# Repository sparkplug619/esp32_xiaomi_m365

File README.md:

attention - last update of this repo - i moved it to gitlab -> https://gitlab.com/esp32m365/esp32_xiaomi_m365_display

# esp32_xiaomi_m365
Sample Project for decoding serial bus data on a Xiaomi M365 Scooter on Espressif ESP32:
- Supports one or two 0.96" 128x64 SSD1306 based OLED screen(s)
- Display connectivity via i2c or spi (spi preffered as it's much faster)
- Firmwareupdates (of the ESP32) can be done over WiFi using ArduinoOTA, Scooterfirmwareupdates are not blocked, can be done the usual way
- Connects to known WiFi Networks or opens it's own SSID in AP Mode
- optional Telnet Servers for debugging
- Config Menu for changing scooter & esp settings
- Supports different Screen Languages, Miles/Kilometers, Wheel Sizes, 10/12s batteries
- Alerts for Low Battery, ESC, BMS Temperature, Cell-Voltage Monitoring,...
- displays speeds above 32.768km/h (set for speeds from 10km/h backwards to 55,44km/h forward, backwardspeed is displayed as a positive number)

# Details
- Telnet on Port 36523 with different Screens
- Telnet on Port 36524 with raw byte dump from M365 Bus ("read only")
- Telnet on Port 36525 with packet decode/dump from M365 Bus ("read only")
- M365 Serial Receiver and Packet decoder into Array per Address
- M365 Data Requestor obey the M365 Bus Timing, does not interfere with Xiaomi's Firmware-Flash process, but can be disabled in the menu (ESP Bus Mode = Passive)
- Data Requestor internally allows subscription to predefined groups of data (e.g. OLED display only needs Cell-Voltage Data when it's displayed) to reduce requested data and therefore get a higher update rate on the interesting data fields.
- Internal Timers/Counters for debugging Receiver/Requestor & Oled-Draw/Transfer Durations - see Telnet/36523 Statistics Screen
- Different Screens for Drive/Stop/Charge/Error/Firmwareupgrade/Locked State/Timeout-Screen
- Alerts: Background Task ("Housekeeper") periodically requests additional data from M365 and validates against tresholds (set in configmenu), shows alert-popup and increases alert-counters
- Popups on screen if alerts occur, alert-counters in data screens when stopped
- Scooter can be locked/unlocked/switched off from config-menu
- Custom Screens for
	- Driving
	- "Stopped" - multiple Data screens when not moving (swipe through them using throttle)
	- "Charging" - in single-screen configuration multiple screens while charging (swipe through them using throttle)
	- Config Menu (push Brake & Throttle at the same time to enter, select items using throttle, change/enter using brake)
 	- "LOCKED" screen mode when scooter has been locked

# Todos
 - add display-sleeptimer - x seconds after last event (gas/brake/throttle/speed/chargerun-plug/telnet/AP-Client Connection & speed = 0)

# Telnet / Debugging Interface
 - Telemetrie Screen shows decoded known values: Batt Voltage, Current, Speed,... 
 - Statistics Screen dumps some internal counters, e.g. Packet Counters, CRC Files, Timing,...
 - ESC/BLE/BMS/"X1" RAW Screens dumps the 512 Byte Array for each device (format "00 00 ...")

 use the letters
  - s,t,e,b,n,x to switch between the screens
  - r to reset statistics & zero m365 data arrays

# Wiring
## Connector in M365 Headunit
M365 has a Serial Data Bus over one Wire (UART in half-duplex mode) between BLE Module and ESC (Motor Controller) and we want to connect the ESP32 to that bus, as well as get Power from the Scooter.
The Connection between BLE-Module and ESC consists of 4 wires, the connection as seen on the BLE Module:
- Ground  (Black, "G")
- One Wire Serial Connection (Yellow, "T", 115200bps, 8n1)
- VBatt (Green, "P", always available)
- 5V (Red, "5", only when scooter is turned on)

## ESP32 Powering
ESP32 needs a Vcc of 3.3V, so you can wire the 5V from M365 to a Vreg for 3.3v which powers the ESP. DO NOT POWER THE ESP32 WITH 5V!

## M365 Serial Data Bus Connection

Other then the VCC which can not be 5V, the ESP32 GPIO Pins can be connected to 5V signals.
So the Serial RX & TX Pins can be directly connected, but to ensure communication on the one-wire uart bus we need 2, to be on the safe side 3 parts:
 - 680R or 1k between RX and M365 Data Bus
 - And a Diode from M365 Data Bus in series with a ~100-200R towards TX Pin of  ESP32
That way Hardware-UART on the ESP32 can be used.

## ESP32 Pin assignment

The ESP32 has a io-switchmatrix, so (nearly) any hardwareunit can be mapped to nearly any pin.
Just be sure to not to use:
 - GPIO_NUM_34 – GPIO_NUM_39 are only GPI - Input, NO OUTPUT, No Pullup or Pulldown!
 - GPIO 6-11 are used by flash - not usable
 - GPIO 0 is for boot/flashing with pullup

# PCB Bugs v180723
 - 1nF or 470pF C from EN towards GND and 12-18k R from EN towards 3.3V are missing (sad copy and paste error)
 - the SOT23 Diode housing might be wrong - depending on your Diode (BAS70xx versions) -> the Diode-Package can be rotated 120° CCW to fix that

# Before Compiling

## Choose your environment  (platformio):
  - PlatformIO supports different (build-)"Environments", you will mostly want to select "m365client" which implements the "client" for a stock m365 scooter and the oled display.
## PATCH your libraries!
  - Plattformio includes my patched Adafuit_SSD1306 library for you, if u are using a different ide, please look in platformio.ini for references to the patches libraries and make sure those are used. In the meanwhile Adafruit updated it's libraries to get rid of the problems, so one day i'll update my code to use the new lib from Adafruit and get rid of the patched libraries.
  - earlier code versions needed some files patched in arduino-esp32 framework in order for correct uart functionality. now i've included the patched UART-Files in this repo, so the patch in arduino-esp32 is not needed anymore (save you time and solves the problem that your other projects would also use that patched framework). But one day when arduino-esp32 framework get's updated this might brake and the files included in this project need to be updated.
  - unfortunately the latest update of platform-io included the arduino-esp32 framework with a broken i2c implementation. This needs to be patched manually, but it fixes a general problem, so this will help your other projects using i2c as well. For patching please see this issue and replace the 4 files as mentioned - otherwise the i2c-display will hang at most restarts: https://github.com/platformio/platform-espressif32/issues/126

## setup individual settings
### ssid's and passwords:
 - please open secrets.h and fill in your own ssid/passwords for client/ap mode and ota updates!
### setup for your hardware
 - copy one of my board*.h files that fits your hardware best, update it for your setup and include this file in definitions.h
 - when updating my code you just need to reapply the include of your boards file in definitions.h

# Support, Questions,...?
 - Telegram Group https://t.me/esp32brain4m365

# Credits & Thanks to
 - Paco Gorina for his research on the protocoll and packet structure (-> http://www.gorina.es/9BMetrics/)
 - CamiAlfa for his research and providing informations about the contents of the packets & arrays (-> https://github.com/CamiAlfa/M365-BLE-PROTOCOL)
 - french translation kindly provided by Technoo' Loggie (Telegram Handle @TechnooLoggie)

# Licensed under Creative Commons V4 - BY NC SA
 - THIS MEANS YOU CAN USE THIS CODE FOR NON COMMERCIAL PURPOSES, HAVE TO RESHARE YOUR MODIFICATIONS AND REFERENCE THIS REPO.

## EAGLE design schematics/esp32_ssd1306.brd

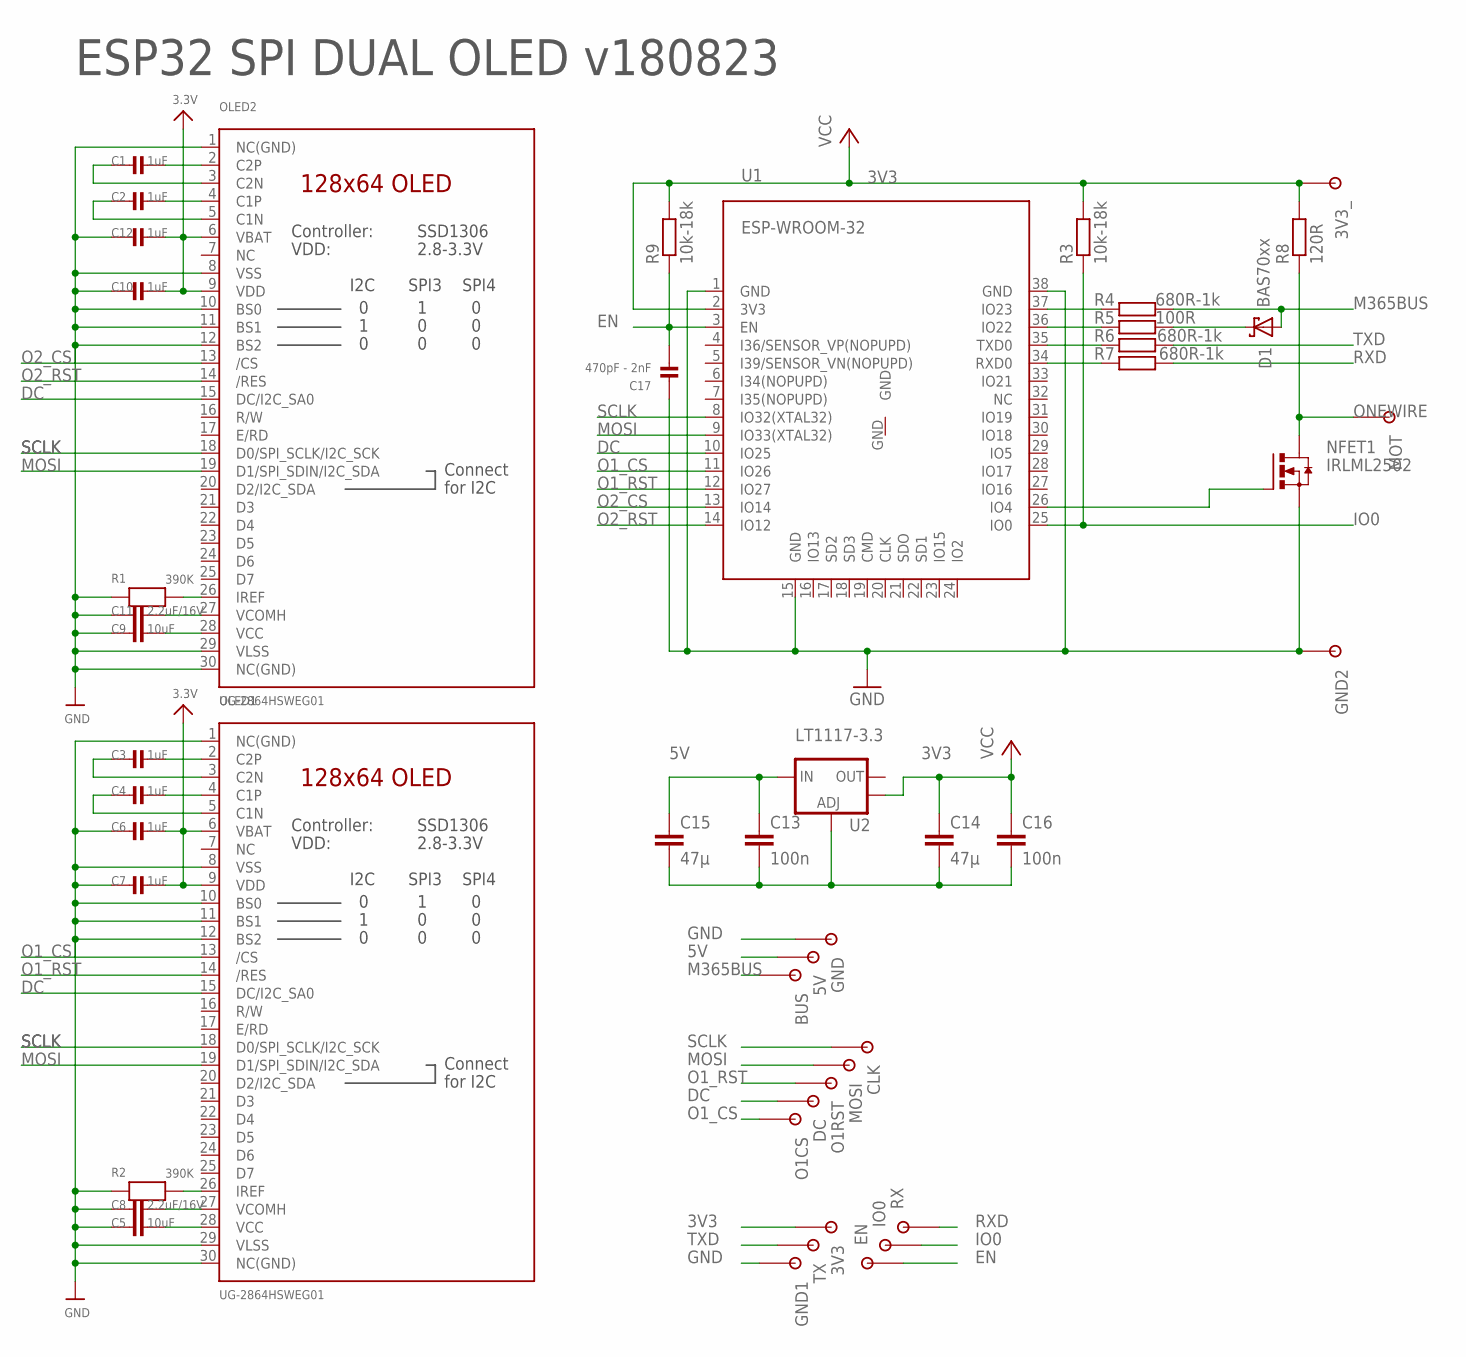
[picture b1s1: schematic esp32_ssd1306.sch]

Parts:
3V3, 3V3_, 5V: PAD1
BUS: PAD1
C1, C2, C3, C4, C6, C7, C10, C12: 1uF; 0805
C5, C9: 10uF; 0805
C8, C11: 2.2uF/16V; 0805
C13, C16: 100n; C0805K
C14, C15: 47µ; C1210K
C17: 470pF - 2nF; 0805
CLK: PAD1
D1: BAS70xx; SOT23
DC: PAD1
EN: PAD1
GND, GND1, GND2: PAD1
IO0: PAD1
MOSI: PAD1
MOT: PAD1
NFET1: IRLML2502; MICRO3
O1CS, O1RST: PAD1
OLED1, OLED2: UG-2864HSWEG01; UG-2864HSWEG01_0.96IN_WRAPAROUND
R1, R2: 390K; 0805
R3, R9: 10k-18k; R0805
R4, R6, R7: 680R-1k; R0805
R5: 100R; R0805
R8: 120R; R0805
RX: PAD1
TX: PAD1
U1: ESP-WROOM-32
U2: LT1117-3.3; SOT223

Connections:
3V3: 3V3.P$1, 3V3_.P$1, C6.2, C7.2, C10.2, C12.2, C14.1, C16.1, OLED1.6 (VBAT), OLED1.9 (VDD), OLED2.6 (VBAT), OLED2.9 (VDD), R3.2, R8.2, R9.2, U1.2 (3V3), U2.4 (OUT)
5V: 5V.P$1, C13.1, C15.1, U2.3 (IN)
DC: DC.P$1, OLED1.15 (DC/I2C_SA0), OLED2.15 (DC/I2C_SA0), U1.10 (IO25)
EN: C17.2, EN.P$1, R9.1, U1.3 (EN)
GND: C5.1, C6.1, C7.1, C8.1, C9.1, C10.1, C11.1, C12.1, C13.2, C14.2, C15.2, C16.2, C17.1, GND.P$1, GND1.P$1, GND2.P$1, NFET1.2 (S), OLED1.1 (NC(GND)), OLED1.8 (VSS), OLED1.10 (BS0), OLED1.11 (BS1), OLED1.12 (BS2), OLED1.29 (VLSS), OLED1.30 (NC(GND)), OLED2.1 (NC(GND)), OLED2.8 (VSS), OLED2.10 (BS0), OLED2.11 (BS1), OLED2.12 (BS2), OLED2.29 (VLSS), OLED2.30 (NC(GND)), R1.1, R2.1, U1.1 (GND), U1.15 (GND), U1.38 (GND), U2.1 (ADJ)
IO0: IO0.P$1, R3.1, U1.25 (IO0)
M365BUS: BUS.P$1, D1.1 (A), R4.2
MOSI: MOSI.P$1, OLED1.19 (D1/SPI_SDIN/I2C_SDA), OLED2.19 (D1/SPI_SDIN/I2C_SDA), U1.9 (IO33(XTAL32))
unnamed: OLED2.26 (IREF), R1.2
unnamed: C1.2, OLED2.2 (C2P)
unnamed: OLED1.26 (IREF), R2.2
unnamed: C3.2, OLED1.2 (C2P)
unnamed: C3.1, OLED1.3 (C2N)
unnamed: C4.2, OLED1.4 (C1P)
unnamed: C4.1, OLED1.5 (C1N)
unnamed: C1.1, OLED2.3 (C2N)
unnamed: C2.2, OLED2.4 (C1P)
unnamed: C2.1, OLED2.5 (C1N)
unnamed: C5.2, OLED1.28 (VCC)
unnamed: C8.2, OLED1.27 (VCOMH)
unnamed: C9.2, OLED2.28 (VCC)
unnamed: C11.2, OLED2.27 (VCOMH)
unnamed: D1.3 (C), R5.2
unnamed: NFET1.1 (G), U1.26 (IO4)
unnamed: R4.1, U1.37 (IO23)
unnamed: R5.1, U1.36 (IO22)
unnamed: R6.1, U1.35 (TXD0)
unnamed: R7.1, U1.34 (RXD0)
O1_CS: O1CS.P$1, OLED1.13 (/CS), U1.11 (IO26)
O1_RST: O1RST.P$1, OLED1.14 (/RES), U1.12 (IO27)
O2_CS: OLED2.13 (/CS), U1.13 (IO14)
O2_RST: OLED2.14 (/RES), U1.14 (IO12)
ONEWIRE: MOT.P$1, NFET1.3 (D), R8.1
RXD: R7.2, RX.P$1
SCLK: CLK.P$1, OLED1.18 (D0/SPI_SCLK/I2C_SCK), OLED2.18 (D0/SPI_SCLK/I2C_SCK), U1.8 (IO32(XTAL32))
TXD: R6.2, TX.P$1

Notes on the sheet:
ESP32 SPI DUAL OLED v180823

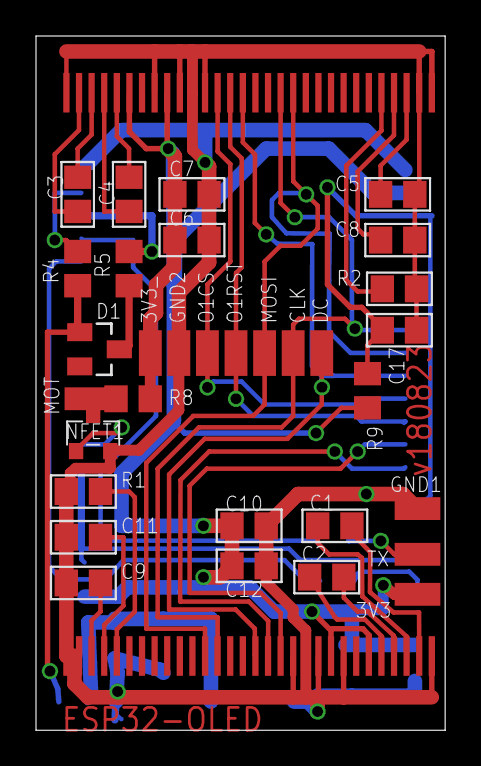
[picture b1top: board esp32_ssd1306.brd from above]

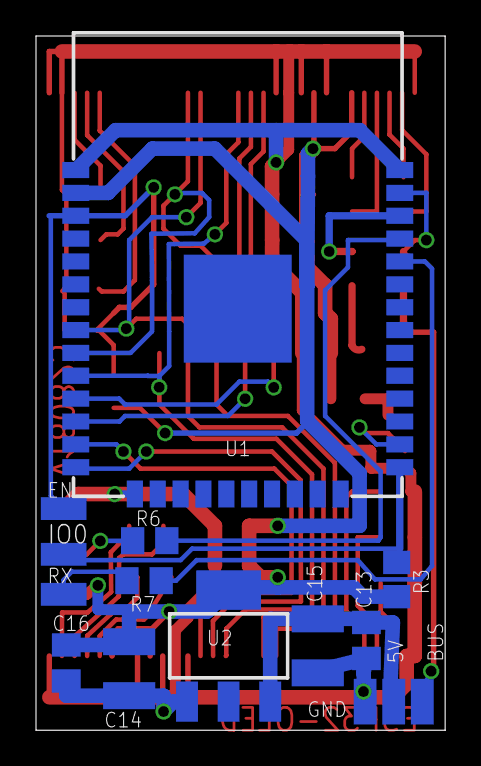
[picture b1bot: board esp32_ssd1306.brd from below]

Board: 2 copper layers, 22.7 x 38.6 mm, 49 parts (17 on the bottom side), 36 nets.

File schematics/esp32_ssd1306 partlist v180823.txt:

Exported from esp32_ssd1306.sch v180823

Part     Value          Device                        Package                          Library              Sheet

ESP32:
U1       ESP-WROOM-32   ESP-WROOM-32                  ESP-WROOM-32                     esp32                1
R6       680R-1k        R-EU_R0805                    R0805                            rcl                  1
R7       680R-1k        R-EU_R0805                    R0805                            rcl                  1
R3       10k-18k        R-EU_R0805                    R0805                            rcl                  1
R9       10k-18k        R-EU_R0805                    R0805                            rcl                  1
C17      470pF - 2nF    CAP_CERAMIC0805               0805                             microbuilder         1

Voltage Regulator:
U2       LT1117-3.3     V_REG_LM1117SOT223            SOT223                           SparkFunEagle-6-6-07 1
C13      100n           C-EUC0805K                    C0805K                           rcl                  1
C14      47µ            C-EUC1210K                    C1210K                           rcl                  1
C15      47µ            C-EUC1210K                    C1210K                           rcl                  1
C16      100n           C-EUC0805K                    C0805K                           rcl                  1

M365 Connection:
R4       680R-1k        R-EU_R0805                    R0805                            rcl                  1
R5       100R           R-EU_R0805                    R0805                            rcl                  1
D1       BAS70xx        BAS70                         SOT23                            diode                1

Needed for OLED Display Connector soldered directly to PCB on Connector OLED1:
OLED1    UG-2864HSWEG01 DISP_OLED_UG-2864HSWEG010.96" UG-2864HSWEG01_0.96IN_WRAPAROUND ssd1306              1
R2       390K           RESISTOR0805                  0805                             microbuilder         1
C3       1uF            CAP_CERAMIC0805               0805                             microbuilder         1
C4       1uF            CAP_CERAMIC0805               0805                             microbuilder         1
C6       1uF            CAP_CERAMIC0805               0805                             microbuilder         1
C7       1uF            CAP_CERAMIC0805               0805                             microbuilder         1
C5       10uF           CAP_CERAMIC0805               0805                             microbuilder         1
C8       2.2uF/16V      CAP_CERAMIC0805               0805                             microbuilder         1

Needed for OLED Display Connector soldered directly to PCB on Connector OLED2:
OLED2    UG-2864HSWEG01 DISP_OLED_UG-2864HSWEG010.96" UG-2864HSWEG01_0.96IN_WRAPAROUND ssd1306              1
R1       390K           RESISTOR0805                  0805                             microbuilder         1
C1       1uF            CAP_CERAMIC0805               0805                             microbuilder         1
C2       1uF            CAP_CERAMIC0805               0805                             microbuilder         1
C12      1uF            CAP_CERAMIC0805               0805                             microbuilder         1
C9       10uF           CAP_CERAMIC0805               0805                             microbuilder         1
C10      1uF            CAP_CERAMIC0805               0805                             microbuilder         1
C11      2.2uF/16V      CAP_CERAMIC0805               0805                             microbuilder         1

Optional (not implemented in Firmware) for Temperature Sensor (1-wire or analog):
NFET1    IRLML2502      IRLML2502                     MICRO3                           transistor-power     1
R8       120R           R-EU_R0805                    R0805                            rcl                  1

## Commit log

2018-07-26 reorganized/updated status screens, new charging screen
2018-07-31 screenformating done, minor bugfixing
2018-08-18 adopted GPIOs for PCB v180723, added SPI for faster display updates
2018-08-23 added schematics v180823
2018-08-25 cleanup/refactoring
2018-08-28 added i2c/spi clock speed for updated ssd1306 library, fixed some minor stuff, added Stauts display to trip (stop) screen
2018-08-29 added support for 10" wheels
2018-08-30 added chargedcapacity, updated charging-screen layout, added some menu handling stuff
2018-08-30 added (readonly) menu-screens, perefences loading/saving
2018-08-31 fixed oled1_rotation definition location
2018-09-02 added partlist
2018-09-02 fixed airwire
2018-09-06 fixed some minor bugs, worked on config menu
2018-09-07 implemented batt/wheel/busmode, fixed wifi-ap bug
2018-09-07 added housekeeper
2018-09-07 added commandsending, added housekeeperrequests
2018-09-07 add lock/unlock/turnoff command
2018-09-10 partly verified previous new implementations (config menu, housekeeper,...)
2018-09-11 implemented rest of menu functions, added lockstate detection and display
2018-09-12 config menu start now via brake & throttle press, reorg of stopsubscreens
2018-09-17 fixed handling of "bothbutton", added oledreinit for fix of sometimes screwed display content
2018-09-28 added config.h (moved config defines from .ino) added strings.h (support for different languages) overhauled display code for strings.h support added configmenu (not finished)
2018-09-28 revised README.md
2018-09-29 added new driving screens
2018-10-08 added locked-screen, cleaned up mixed fonts, fixed power-display casting error
2018-10-09 added popup code
2018-10-19 fixed drivescreen current/watt casting
2018-10-21 finished menu display, value changing, implemented throttle min/max learning, fixed alert-treshold comparison for cell-voltage-difference-alert... ...
2018-10-21 fixed throttlemin / screen-navigation error
2018-10-21 fixed charging display while scooter is locked
2018-10-21 added battery low voltage alarm to configmenu
2018-10-21 change popup to alert & info popup configmenu: added option to beep on alert (for alertpopup) changed commandsending methods for esc & x1 commands fixed alerts on startup (as long as no values have b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
2018-10-24 shortened strings, moved value-edit dialog to 2nd screen on dualscreensetup, added configmenu autoexit if speed > 5km/h, minor changed to screen-switching conditions
2018-10-24 disabled popupdisplay while changing values, fixed menu-navigation-lock while changing values
2018-10-25 added fonts
2018-10-31 splitted .ino in c++/header files
2018-10-31 added License - CC BY NC SA
2018-10-31 added support for different screen-languages
2018-11-01 added german & french translations
2018-11-01 fixed accidental typo/bug
2018-11-01 fixed formating bug on 2nd oled display/assets screen
2018-11-01 added german and french strings
2018-11-01 added credits, license, telegram group info
2018-11-01 minor french strings update
2018-11-02 added patch for speeds > 32.768km/h
2018-11-03 semi-working onewire uart
2018-11-07 added info about boards.h, added secrets.h
2018-11-10 new init-code, .ino smaller, ota now in wlan.cpp, display-init in display.cpp and non-blocking start-screen
2018-11-10 minor update...
2018-11-10 switched to plattformio style
2018-11-10 added platformio.ini to repo
2018-12-13 added boards definition files
2018-12-13 updated config with gpio definitions, currently unused (waiting for webserver feature)
2018-12-13 updated definitions.h
2018-12-13 updated display - moved code to class, restructured for easier integration of other displays, added "screentemplate" functions
2018-12-13 added patched uart files from arduino-esp32 - this repo does not need a patched arduino-esp32 framework anymore.
2018-12-13 removed old m365 implementation, added new m365 client class
2018-12-13 updated misc files to use new m365client class and display class
2018-12-13 updated platformio-environments
